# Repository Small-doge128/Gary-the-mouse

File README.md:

# about
A custom mouse that's small and lightweight like a cookie, a little inspiration is from the zero mouse. It's my second using kicad, but it still took a lot of time. Also i used [this repository](https://github.com/badjeff/paw3395-pcb) for the sensor pcb.

# features
A powerful microcontroller with bluetooth and usb-c for charging the lipo battery, nice scroll wheel encoder, optical sensor with up to 12 000 dpi which is low power and sometimes used for gaming and four small micro switches, two for main and other two for the side buttons, you can map them however you want. Last but really good is a build in LED in the microcontroller that is the normal red, yellow and green

# step by step tutorial for firmware
1 - download the file called firmware.uF2   
2 - connect your seeed studio via usb-c                                                                                                                                               
3 - put it into bootloader mode (double tap the **RESET** button the build in led shall start pulsing).                                                                                 
4 - now open your file manager and you should see a new USB drive called `XIAO-BLE`     
5 - drag and drop the file we installed earlier into it and the USB drive should dissaper which means **good** now it shloud work **enjoy**

# dimensions
pcb - 49.5 mm and 50 mm

# why did i create it
My mouse is not that bad, but my felt that it was heavy and actually when I take the top cover off It's more comfortable. I did weanted to spice it up with my preferences, so It's more like my mouse then a customer mouse and I know I had the skills to make that, but still I've learnt a lot.

# pictures

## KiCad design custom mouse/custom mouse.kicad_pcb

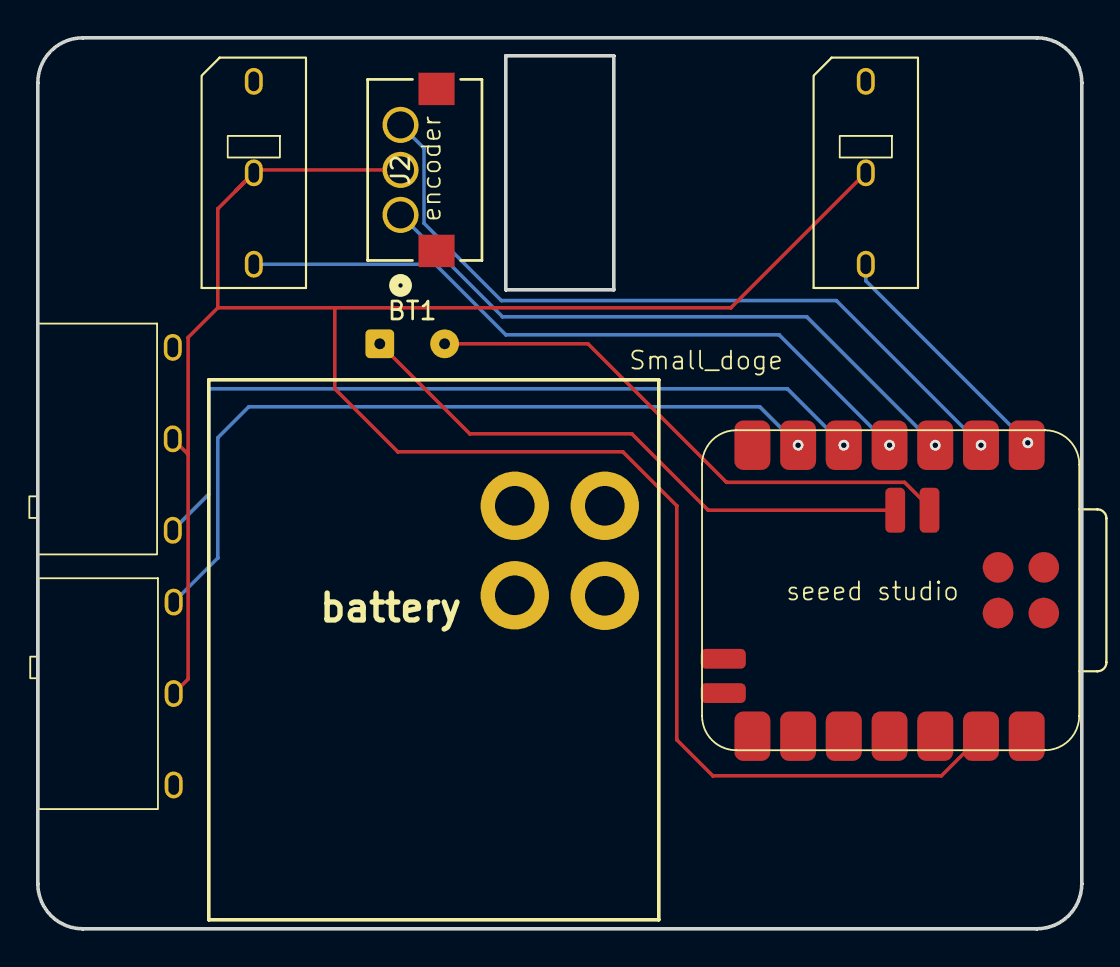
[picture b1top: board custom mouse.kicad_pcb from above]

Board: 2 copper layers, 58.0 x 49.5 mm, 11 parts (0 on the bottom side), 9 nets.

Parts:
BT1: Battery_Cell; SolderWire-0.1sqmm_1x02_P3.6mm_D0.4mm_OD1mm
H1, H2, H3, H4: MountingHole; MountingHole_2.2mm_M2_DIN965_Pad
J2: EC10E1220501; CONN03_EC10E_9P8X6P1_ALPS
SW6, SW7: SW_Push_SPDT; KailhSw
SW8, SW9: SW_Push_SPDT; KailhSw sidemount
U1: XIAO-nRF52840-DIP; XIAO-nRF52840-SMD

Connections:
/pin 1: SW6.3 (C), U1.1 (P0.02_A0_D0)
/pin 2: J2.3, U1.2 (P0.03_A1_D1)
/pin 3: J2.1, U1.3 (P0.28_A2_D2)
/pin 4: SW7.3 (C), U1.4 (P0.29_A3_D3)
/pin 5: SW8.3 (C), U1.5 (P0.04_A4_D4_SDA)
/pin 6: SW9.1 (A), U1.6 (P0.05_A5_D5_SCL)
unnamed: BT1.1 (+), U1.hy
unnamed: BT1.2 (-), U1.20
unnamed: J2.2, SW6.2 (B), SW7.2 (B), SW8.2 (B), SW9.2 (B), U1.13 (GND)
